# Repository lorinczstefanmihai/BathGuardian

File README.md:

# 🛁 Bath Guardian – AWS IoT Edition ( THIS IS THE PROTOTYPE)

An ESP32-powered monitoring & automation system for humidity, gas levels, temperature, and bathroom safety.

Bath Guardian uses an ESP32 microcontroller, environmental sensors, and AWS IoT Core to provide real-time monitoring, automation, and remote control. The system can operate both locally (via its built-in web server) and through the cloud.

## 🚀 System Architecture Overview
ESP32 (AP/STA Mode)
The ESP32 runs in dual AP/STA mode, allowing it to connect to your Wi-Fi network while also offering an access point for local setup or fallback access.

## 🔧 Hardware Components
🌡️ Sensors

DHT11 – Temperature & humidity

MQ-series gas sensor – Detects gases/VOCs (steam, odors, poor air quality)

The ESP32 collects continuous sensor data and pushes it to the cloud.

## 🌈 RGB LED

Provides visual indicators for system status, warnings, or mode states.

🔌 Relay Outputs

Controls:

Ventilation fan

Lighting

Relays can be triggered automatically (based on sensor thresholds) or remotely via AWS IoT commands.

## ☁️ AWS Cloud Integration

Bath Guardian connects to the cloud using:

AWS IoT Core (MQTT)

The ESP32 publishes data to custom MQTT topics.
Example topic used:

test_topic/esp32

AWS IoT Core receives these messages for monitoring, automation, and further processing.

## 🖥️ Local Web Interface

The ESP32 also hosts a local HTTP web server, accessible over Wi-Fi.

Features:

Live sensor reading display

Local configuration

This allows full control even without internet.

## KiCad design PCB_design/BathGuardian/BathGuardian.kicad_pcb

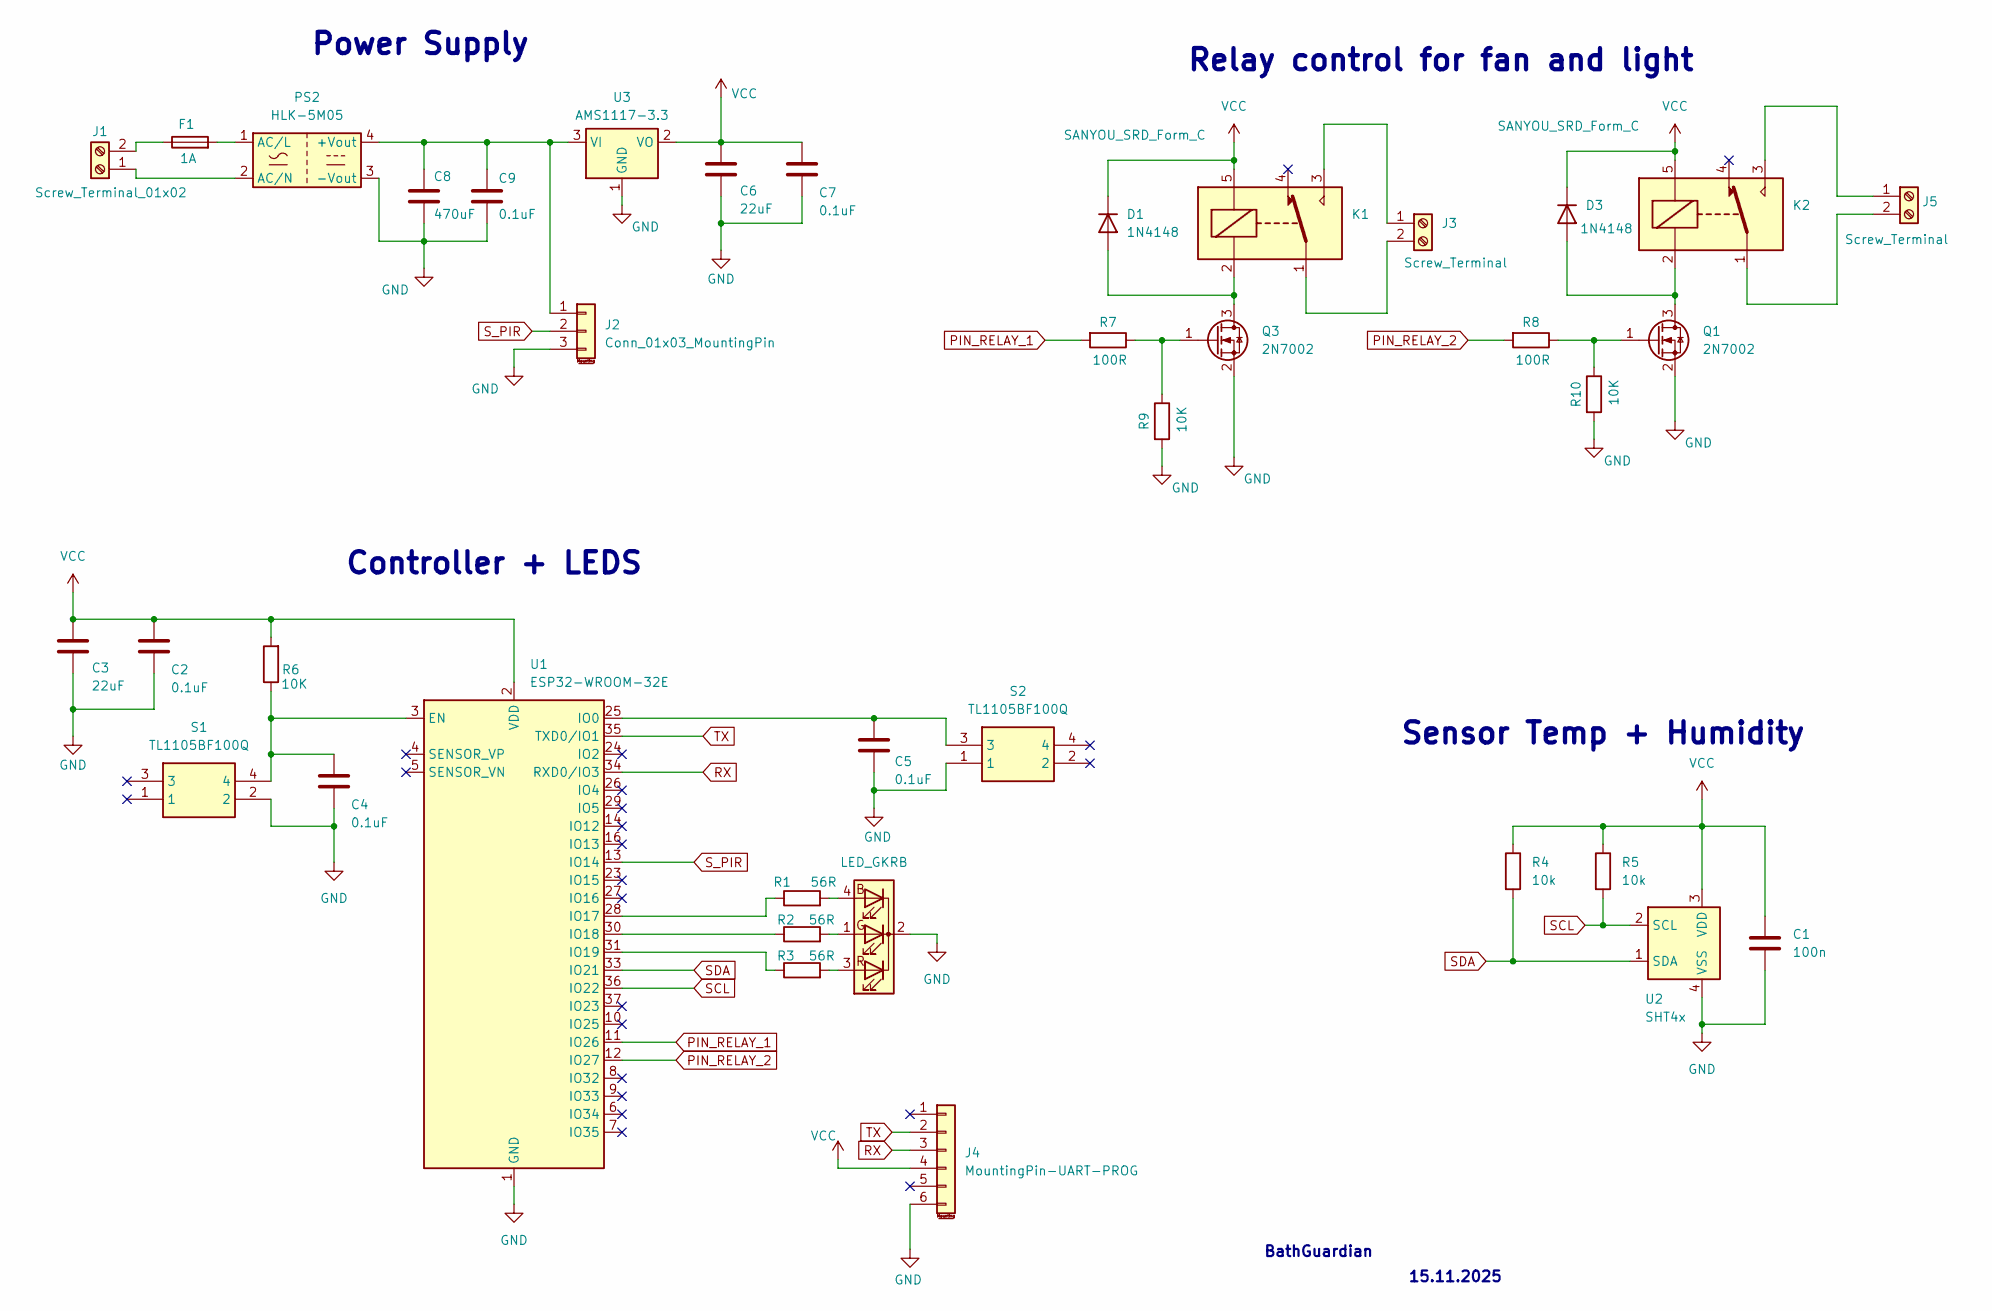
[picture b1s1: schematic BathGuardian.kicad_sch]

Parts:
C1: 100n; C_0805_2012Metric
C2, C4, C5, C7, C9: 0.1uF; C_0805_2012Metric
C3, C6: 22uF; C_0805_2012Metric
C8: 470uF; C_0805_2012Metric
D1, D3: 1N4148; Nexperia_CFP3_SOD-123W
D2: LED_GKRB; LED_D5.0mm-4_RGB
F1: 1A; Fuseholder_Cylinder-5x20mm_Stelvio-Kontek_PTF78_Horizontal_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
J1: Screw_Terminal_01x02; KF1282542P
J2: Conn_01x03_MountingPin; PinHeader_1x03_P2.54mm_Vertical
J3, J5: Screw_Terminal; KF1282542P
J4: MountingPin-UART-PROG; PinSocket_1x06_P2.54mm_Vertical
K1, K2: SANYOU_SRD_Form_C; Relay_SPDT_SANYOU_SRD_Series_Form_C
PS2: HLK-5M05; Converter_ACDC_Hi-Link_HLK-5Mxx
Q1, Q3: 2N7002; SOT-23
R1: 56R; R_0805_2012Metric
R2, R3: 56R; LED_0805_2012Metric
R4, R5: 10k; R_0805_2012Metric
R6, R9, R10: 10K; R_0805_2012Metric
R7, R8: 100R; R_0805_2012Metric
S1, S2: TL1105BF100Q; Mouser Part Number 612-TL1105BF100
U1: ESP32-WROOM-32E
U2: SHT4x; Sensirion_DFN-4_1.5x1.5mm_P0.8mm_SHT4x_NoCentralPad
U3: AMS1117-3.3; SOT-223-3_TabPin2

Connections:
GND: C1.2, C2.2, C3.2, C4.2, C5.2, C6.2, C7.2, C8.2, C9.2, D2.2 (K), J2.3, J4.6, PS2.3 (-Vout), Q1.2 (S), Q3.2 (S), R9.2, R10.2, S1.2, S2.1, U1.1 (GND), U1.15 (GND), U1.38 (GND), U1.39 (GND), U2.4 (VSS), U3.1 (GND)
unnamed: D1.2 (A), K1.2, Q3.3 (D)
unnamed: D2.4 (BA), R1.2
unnamed: D2.1 (GA), R2.2
unnamed: D2.3 (RA), R3.2
unnamed: D3.2 (A), K2.2, Q1.3 (D)
unnamed: J1.1, PS2.2 (AC/N)
unnamed: F1.1, J1.2
unnamed: C8.1, C9.1, J2.1, PS2.4 (+Vout), U3.3 (VI)
unnamed: J3.1, K1.3
unnamed: J3.2, K1.1
unnamed: J5.1, K2.3
unnamed: J5.2, K2.1
unnamed: F1.2, PS2.1 (AC/L)
unnamed: Q1.1 (G), R8.1, R10.1
unnamed: Q3.1 (G), R7.1, R9.1
unnamed: C4.1, R6.1, S1.4, U1.3 (EN)
unnamed: C5.1, S2.3, U1.25 (IO0)
unnamed: R1.1, U1.28 (IO17)
unnamed: R2.1, U1.30 (IO18)
unnamed: R3.1, U1.31 (IO19)
PIN_RELAY_1: R7.2, U1.11 (IO26)
PIN_RELAY_2: R8.2, U1.12 (IO27)
RX: J4.3, U1.34 (RXD0/IO3)
SCL: R5.2, U1.36 (IO22), U2.2 (SCL)
SDA: R4.2, U1.33 (IO21), U2.1 (SDA)
S_PIR: J2.2, U1.13 (IO14)
TX: J4.2, U1.35 (TXD0/IO1)
VCC: C1.1, C2.1, C3.1, C6.1, C7.1, D1.1 (K), D3.1 (K), J4.4, K1.5, K2.5, R4.1, R5.1, R6.2, U1.2 (VDD), U2.3 (VDD), U3.2 (VO)

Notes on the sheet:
Sensor Temp + Humidity
Controller + LEDS
BathGuardian
Relay control for fan and light
15.11.2025
Power Supply

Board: 2 copper layers, 38 parts (0 on the bottom side), 29 nets, no tracks yet.

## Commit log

2025-10-16 WiFi App done
2025-10-17 sdk update after adding HTTP server component
2025-10-18 hhtp server + ota + mq135 + dht11
2025-10-29 Adding comments
2025-10-29 adding get function for data to send to rest api interface
2025-10-29 adding handlers for rest api interface and connect/disconnect function to the router as a station mode and to access internet
2025-10-29 Wifi connect and disconnect to the router as a station mode ( internet connection )
2025-10-29 local webpage update
2025-10-29 documents with presentation added
2025-10-30 Comment modifcations
2025-10-30 Saving credentials to the nvs
2025-11-23 aws done
2025-11-23 Revise README for Bath Guardian project overview
    Updated the README to provide a comprehensive overview of the Bath Guardian system, including hardware components, system architecture, and AWS cloud integration.
2025-11-23 Remove Bath Guardian project details from README
    Removed detailed description and images related to the Bath Guardian project.
